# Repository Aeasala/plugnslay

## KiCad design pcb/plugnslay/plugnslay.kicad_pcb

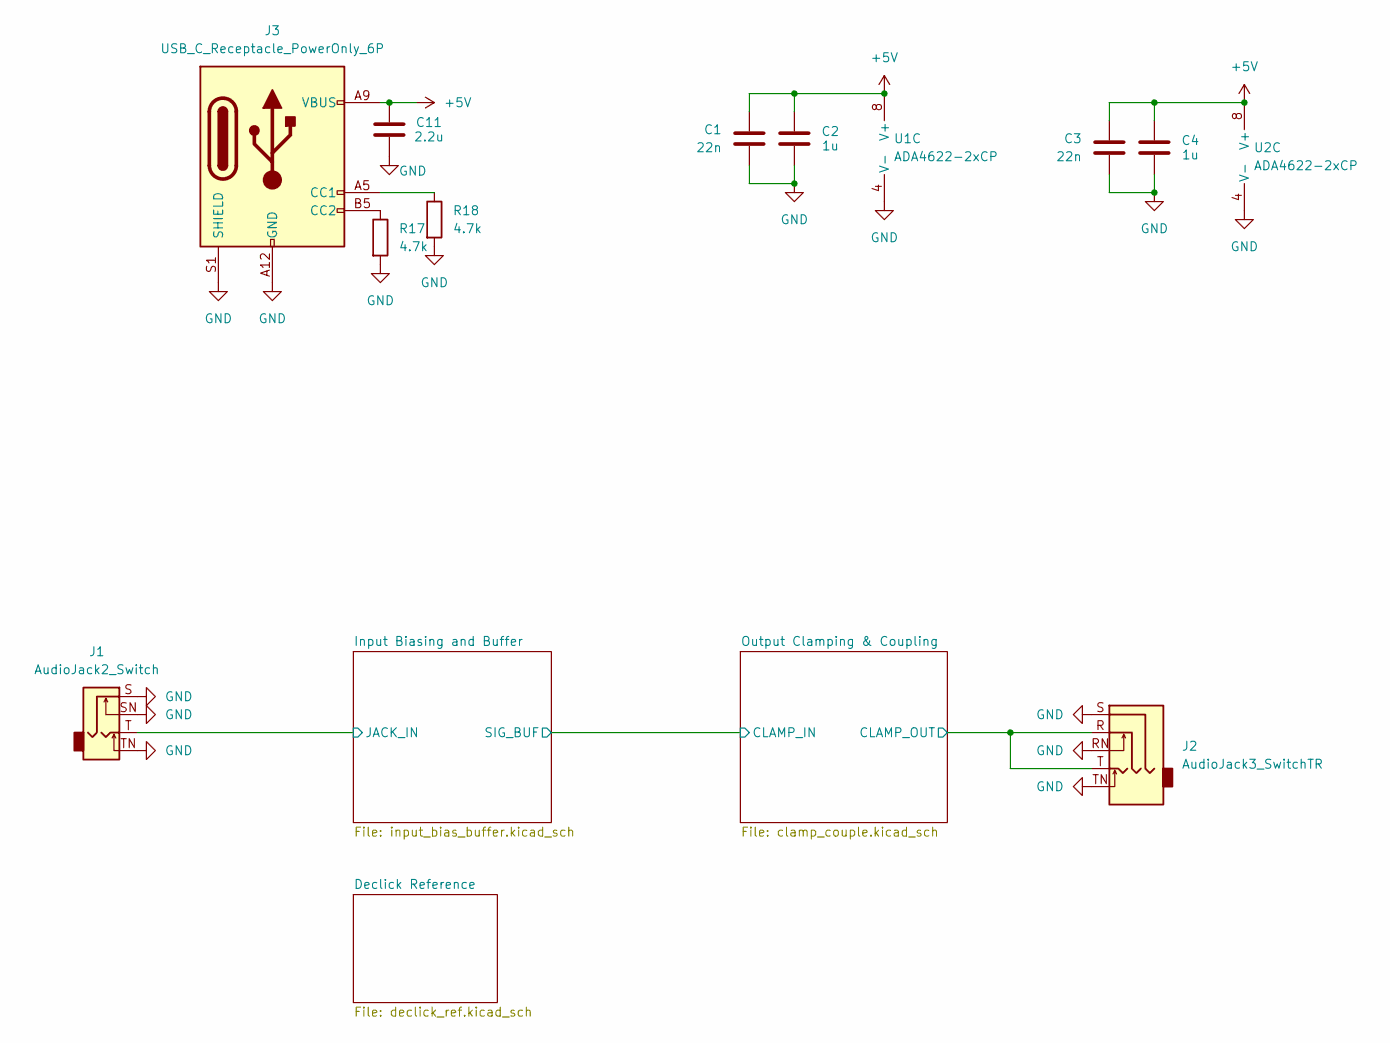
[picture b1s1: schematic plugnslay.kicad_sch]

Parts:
C1, C3: 22n; C_1206_3216Metric_Pad1.33x1.80mm_HandSolder; Part Number C1206C223K3RACTU
C2, C4: 1u; C_1206_3216Metric_Pad1.33x1.80mm_HandSolder; Part Number C1206C105K4RAC
C11: 2.2u; C_1206_3216Metric_Pad1.33x1.80mm_HandSolder; Part Number C1206C225K4RACTU
J1: AudioJack2_Switch; Jack_6.35mm_Neutrik_NRJ4HF_Horizontal; Part Number NRJ4HF
J2: AudioJack3_SwitchTR; Jack_3.5mm_CUI_SJ1-3535NG_Horizontal_CircularHoles; Part Number SJ1-3535NG
J3: USB_C_Receptacle_PowerOnly_6P; USB_C_Receptacle_GCT_USB4125-xx-x-0190_6P_TopMnt_Horizontal; Part Number USB4125-GF-A
R17, R18: 4.7k; R_1206_3216Metric_Pad1.30x1.75mm_HandSolder; Part Number CRCW12064K70FKEA
U1, U2: ADA4622-2xCP; SOIC-8_3.9x4.9mm_P1.27mm; Part Number ADA4622-2ARZ-R7

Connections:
+5V: C1.1, C2.2, C3.1, C4.2, C11.1, J3.A9 (VBUS), J3.B9 (VBUS), U1.8 (V+), U1.9 (V+), U2.8 (V+), U2.9 (V+); also elsewhere on the board
/Input Biasing and Buffer/JACK_IN: J1.T; also elsewhere on the board
/Output Clamping & Coupling/CLAMP_OUT: J2.R, J2.T; also elsewhere on the board
GND: C1.2, C2.1, C3.2, C4.1, C11.2, J1.S, J1.SN, J1.TN, J2.RN, J2.S, J2.TN, J3.A12 (GND), J3.B12 (GND), J3.S1 (SHIELD), R17.2, R18.2, U1.4 (V-), U2.4 (V-); also elsewhere on the board
unnamed: J3.A5 (CC1), R18.1
unnamed: J3.B5 (CC2), R17.1

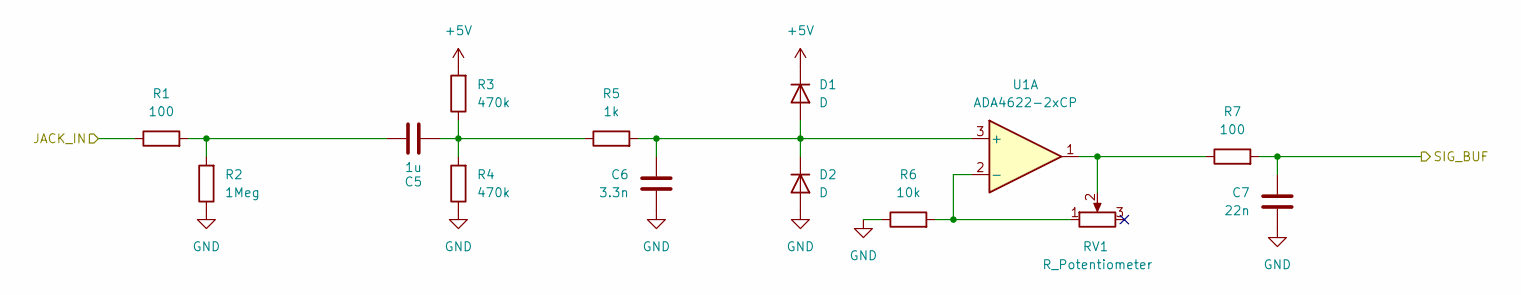
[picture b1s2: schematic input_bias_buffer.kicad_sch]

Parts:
C5: 1u; C_1206_3216Metric_Pad1.33x1.80mm_HandSolder; Part Number C1206C105K4RAC
C6: 3.3n; C_1206_3216Metric_Pad1.33x1.80mm_HandSolder; Part Number C1206C332K3RACTU
C7: 22n; C_1206_3216Metric_Pad1.33x1.80mm_HandSolder; Part Number C1206C223K3RACTU
D1, D2: D; D_SOD-123; Part Number 1N4448W-HE3_A-08
R1, R7: 100; R_1206_3216Metric_Pad1.30x1.75mm_HandSolder; Part Number CRCW1206100RFKEA
R2: 1Meg; R_1206_3216Metric_Pad1.30x1.75mm_HandSolder; Part Number CRCW12061M00FKEA
R3, R4: 470k; R_1206_3216Metric_Pad1.30x1.75mm_HandSolder; Part Number CRCW1206470KFKEA
R5: 1k; R_1206_3216Metric_Pad1.30x1.75mm_HandSolder; Part Number CRCW12061K00FKEA
R6: 10k; R_1206_3216Metric_Pad1.30x1.75mm_HandSolder; Part Number CRCW120610K0FKEA
RV1: R_Potentiometer; Potentiometer_Bourns_PTV09A-1_Single_Vertical; Part Number PTV09A-2020S-B503
U1: ADA4622-2xCP; SOIC-8_3.9x4.9mm_P1.27mm; Part Number ADA4622-2ARZ-R7

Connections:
+5V: D1.1 (K), R3.2; also elsewhere on the board
/Input Biasing and Buffer/JACK_IN: R1.1; also elsewhere on the board
/Input Biasing and Buffer/SIG_BUF: C7.2, R7.2; also elsewhere on the board
GND: C6.1, C7.1, D2.2 (A), R2.1, R4.1, R6.1; also elsewhere on the board
unnamed: C5.1, R1.2, R2.2
unnamed: C5.2, R3.1, R4.2, R5.1
unnamed: C6.2, D1.2 (A), D2.1 (K), R5.2, U1.3 (+)
unnamed: R7.1, RV1.2, U1.1
unnamed: R6.2, RV1.1, U1.2 (-)

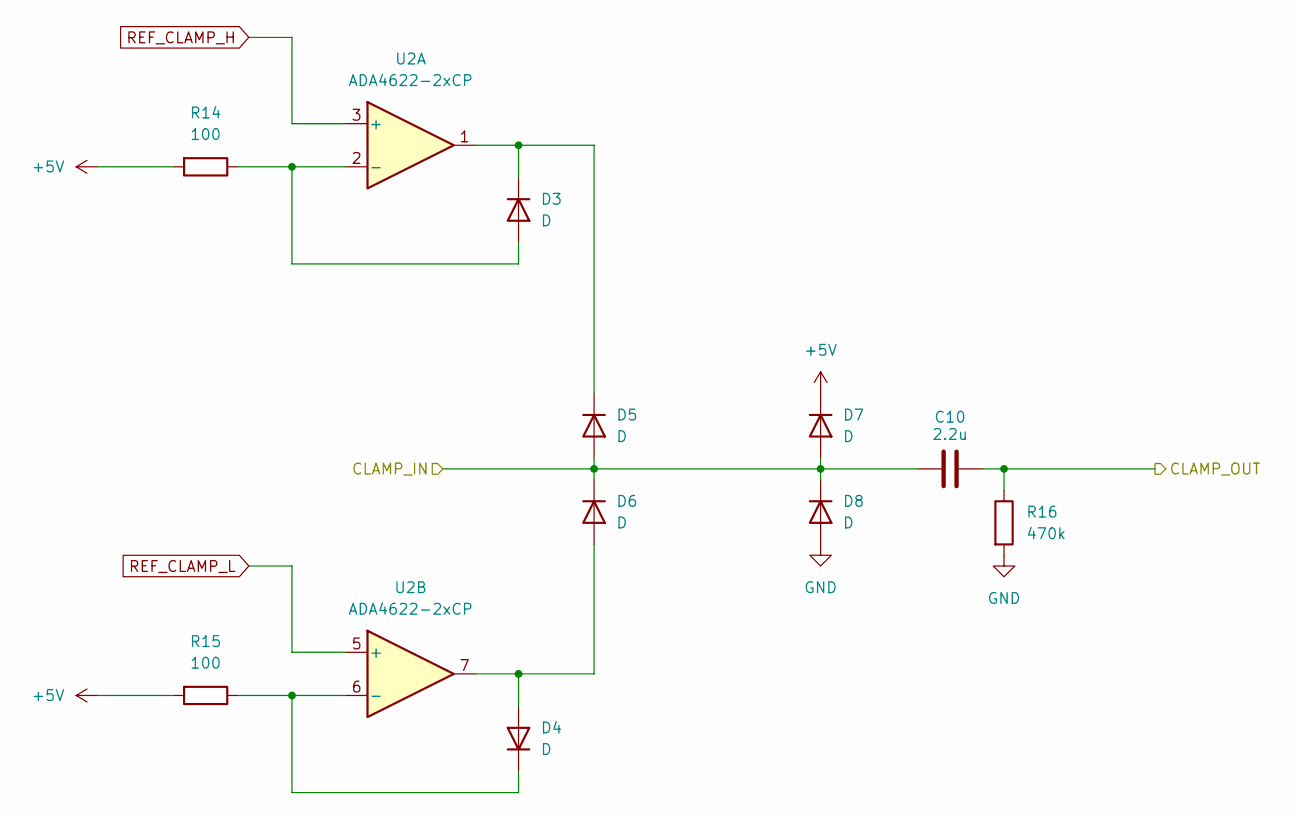
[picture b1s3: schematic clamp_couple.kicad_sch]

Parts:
C10: 2.2u; C_1206_3216Metric_Pad1.33x1.80mm_HandSolder; Part Number C1206C225K4RACTU
D3, D4, D5, D6, D7, D8: D; D_SOD-123; Part Number 1N4448W-HE3_A-08
R14, R15: 100; R_1206_3216Metric_Pad1.30x1.75mm_HandSolder; Part Number CRCW1206100RFKEA
R16: 470k; R_1206_3216Metric_Pad1.30x1.75mm_HandSolder; Part Number CRCW1206470KFKEA
U2: ADA4622-2xCP; SOIC-8_3.9x4.9mm_P1.27mm; Part Number ADA4622-2ARZ-R7

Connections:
+5V: D7.1 (K), R14.2, R15.2; also elsewhere on the board
/Input Biasing and Buffer/SIG_BUF: C10.2, D5.2 (A), D6.1 (K), D7.2 (A), D8.1 (K); also elsewhere on the board
/Output Clamping & Coupling/CLAMP_OUT: C10.1, R16.1; also elsewhere on the board
GND: D8.2 (A), R16.2; also elsewhere on the board
unnamed: D3.2 (A), R14.1, U2.2 (-)
unnamed: D3.1 (K), D5.1 (K), U2.1
unnamed: D4.2 (A), D6.2 (A), U2.7
unnamed: D4.1 (K), R15.1, U2.6 (-)
REF_CLAMP_H: U2.3 (+); also elsewhere on the board
REF_CLAMP_L: U2.5 (+); also elsewhere on the board

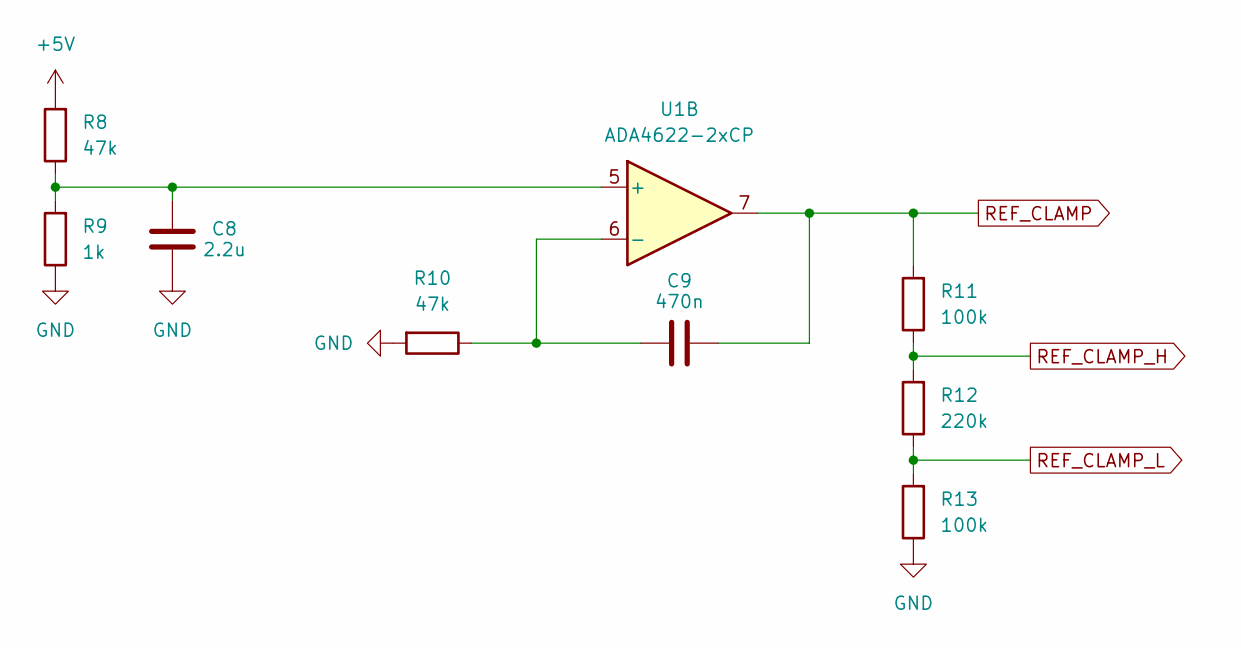
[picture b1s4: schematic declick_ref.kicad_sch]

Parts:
C8: 2.2u; C_1206_3216Metric_Pad1.33x1.80mm_HandSolder; Part Number C1206C225K4RACTU
C9: 470n; C_1206_3216Metric_Pad1.33x1.80mm_HandSolder; Part Number C1206C474K3RAC
R8, R10: 47k; R_1206_3216Metric_Pad1.30x1.75mm_HandSolder; Part Number CRCW120647K0FKEA
R9: 1k; R_1206_3216Metric_Pad1.30x1.75mm_HandSolder; Part Number CRCW12061K00FKEA
R11, R13: 100k; R_1206_3216Metric_Pad1.30x1.75mm_HandSolder; Part Number CRCW1206100KFKEAC
R12: 220k; R_1206_3216Metric_Pad1.30x1.75mm_HandSolder; Part Number CRCW1206220KFKEA
U1: ADA4622-2xCP; SOIC-8_3.9x4.9mm_P1.27mm; Part Number ADA4622-2ARZ-R7

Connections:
+5V: R8.2; also elsewhere on the board
GND: C8.1, R9.1, R10.2, R13.1; also elsewhere on the board
unnamed: C8.2, R8.1, R9.2, U1.5 (+)
unnamed: C9.2, R10.1, U1.6 (-)
REF_CLAMP: C9.1, R11.2, U1.7
REF_CLAMP_H: R11.1, R12.2; also elsewhere on the board
REF_CLAMP_L: R12.1, R13.2; also elsewhere on the board

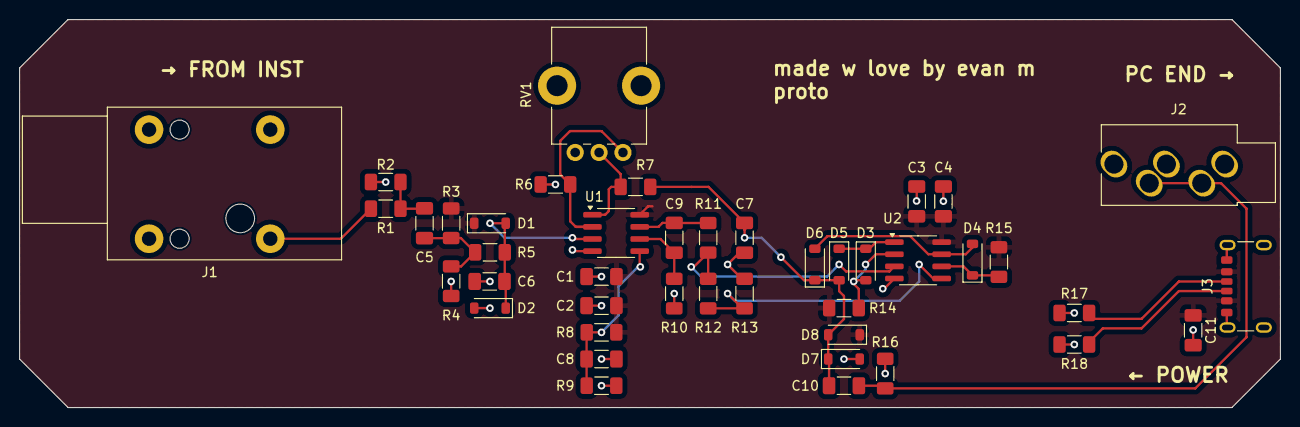
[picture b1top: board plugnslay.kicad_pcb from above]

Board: 2 copper layers, 132.1 x 40.6 mm, 43 parts (0 on the bottom side), 21 nets.

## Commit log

2024-08-20 kicad port
2024-08-21 complete first prototype
2024-08-21 bom and tweak links
2024-08-21 fix pot ref, gen gerbers
2024-08-21 non clamping non declick demo of sim
2024-08-21 fix silk label for power
